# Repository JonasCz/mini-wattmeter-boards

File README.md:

# Simple DC wattmeter:

Status: in progress, untested, unfinished

Screenshot: 

Components:

* STM8S003 microcontroller
* INA240 current shunt sense
* NCP781 5v linear regulator

Features:

* Configurable with solder-jumpers, to show:
   * Volts
   * Watts
   * Amps
   * Watt-hours
   * Amp-hours

* Minimal STM8 + segment LED display
* Linear-regulator powered (max current?) - need to check, tricks with cpu sleep, display dimming on high voltage? Or zener diode + resistor pre-regulator
* XT60 in - out
* Serial ouptut multiplexed onto segment outputs, activated only between digit cycle somehow? (or ability to choose serial ouptut instead of digits?)

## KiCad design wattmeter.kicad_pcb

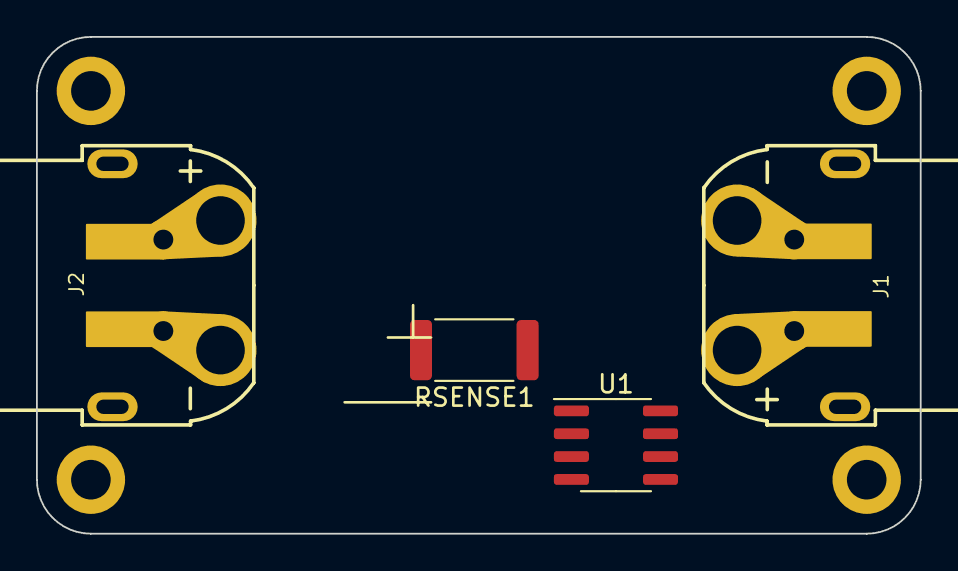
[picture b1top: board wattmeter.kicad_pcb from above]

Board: 2 copper layers, 49.1 x 27.6 mm, 4 parts (0 on the bottom side), 3 nets, no tracks yet.

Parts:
J1, J2: Conn_01x02; Amass_XT60PW-M_Kombifootprint
RSENSE1: 0.005; R_2512_6332Metric
U1: INA240A2D; SOIC-8_3.9x4.9mm_P1.27mm

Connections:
unnamed: J1.2, RSENSE1.1
unnamed: J2.2, RSENSE1.2
unnamed: U1.2 (GND), U1.4 (GND)

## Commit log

2022-06-07 add screenshot
